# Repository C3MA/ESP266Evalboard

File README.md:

# ESP8266Evalboard

The purpose of this project is to provide open source based home automation inspiration. It consists of one or more ESP8266 evaluation boards with sensors and actors which connect to a raspberry pi with openhab.

For further documentation, look up the Docu folder in this repository.

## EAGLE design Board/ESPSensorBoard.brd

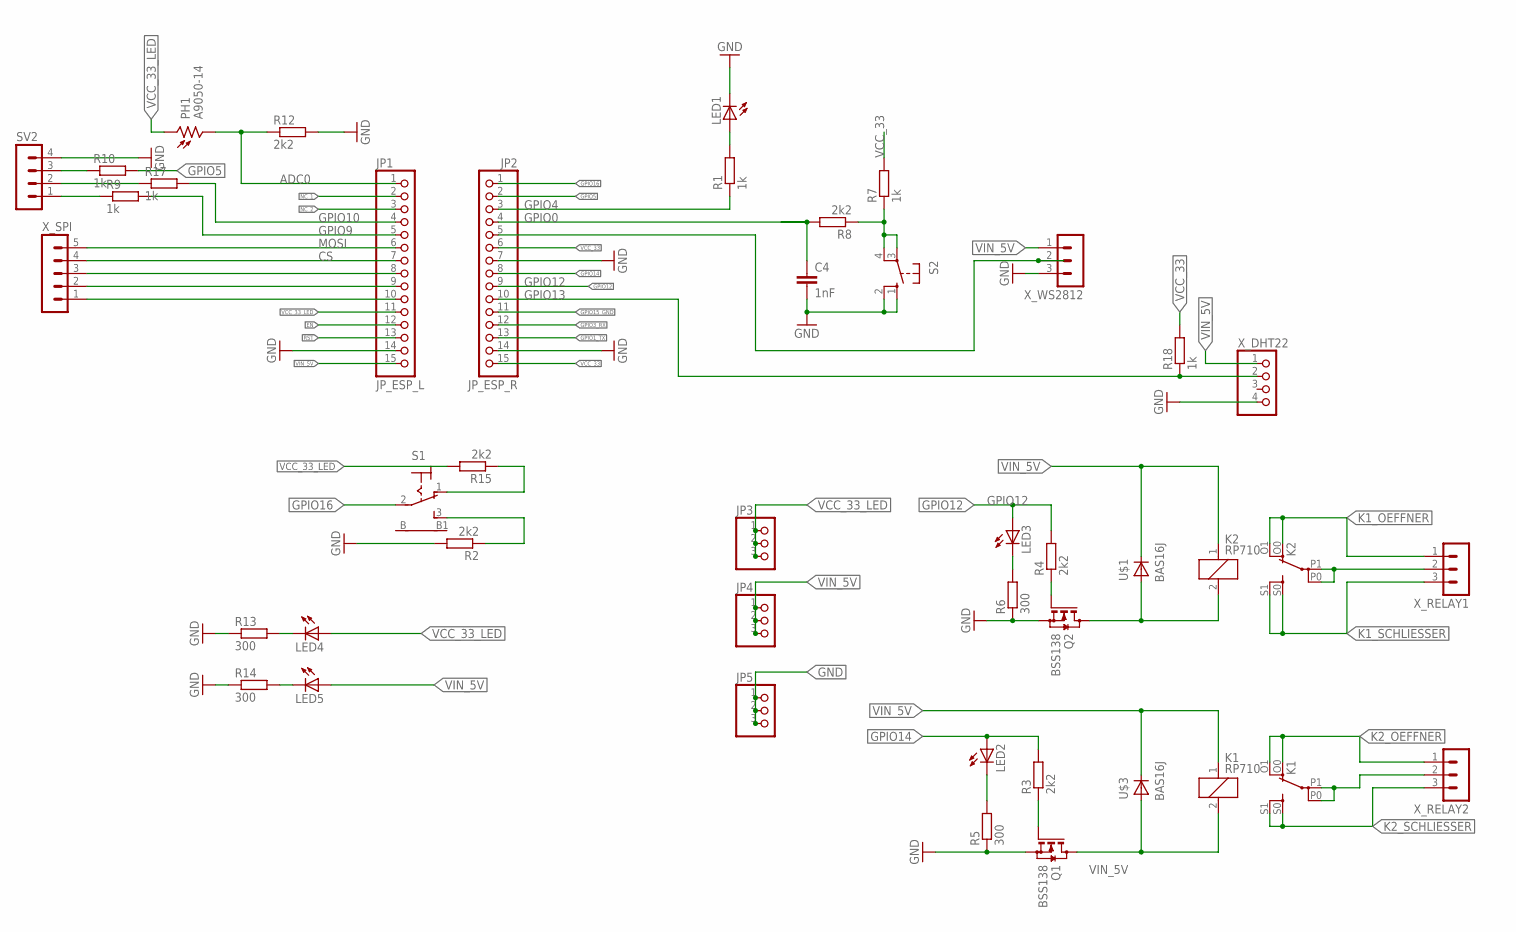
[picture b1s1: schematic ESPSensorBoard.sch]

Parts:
C4: 1nF; C0805K
JP1: JP_ESP_L; 1X15
JP2: JP_ESP_R; 1X15
JP3, JP4, JP5: PINHD-1X3; 1X03
K1, K2: RP710
LED1: LED5MM
LED2, LED3, LED4, LED5: LED3MM
PH1: A9050-14; M9960
Q1, Q2: BSS138; SOT23
R1, R7, R9, R10, R17, R18: 1k; R0805
R2, R3, R4, R8, R12, R15: 2k2; R0805
R5, R6, R13, R14: 300; R0805
S1: LPV-1
S2: 10-XX; B3F-10XX
SV2: MA04-1
U$1, U$3: BAS16J; 0805-POL
X_DHT22: PINHD-1X4; 1X04
X_RELAY1, X_RELAY2: MA03-1
X_SPI: MA05-1
X_WS2812: MA03-1

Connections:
ADC0: JP1.1, PH1.2, R12.1
CS: JP1.7, X_SPI.4
EN: JP1.12
GND: C4.2, JP1.14, JP2.7, JP2.14, JP5.1, JP5.2, JP5.3, LED1.K (C), Q1.2 (S), Q2.2 (S), R2.2, R5.1, R6.1, R12.2, R13.1, R14.1, S2.1 (S), S2.2 (S1), SV2.4, X_DHT22.4, X_WS2812.3
GPIO0: C4.1, JP2.4, R8.2
GPIO1_TX: JP2.13
GPIO2: JP2.5, X_WS2812.2
GPIO3_RX: JP2.12
GPIO4: JP2.3, R1.1
GPIO5: JP2.2, R10.2
GPIO9: JP1.5, R9.2
GPIO10: JP1.4, R17.2
GPIO12: JP2.9, LED3.A, R4.2
GPIO13: JP2.10, R18.1, X_DHT22.2
GPIO14: JP2.8, LED2.A, R3.2
GPIO15_GND: JP2.11
GPIO16: JP2.1, S1.2
K1_OEFFNER: K2.O0 (O), K2.O1 (O), X_RELAY1.1
K1_SCHLIESSER: K2.S0 (S), K2.S1 (S), X_RELAY1.3
K2_OEFFNER: K1.O0 (O), K1.O1 (O), X_RELAY2.1
K2_SCHLIESSER: K1.S0 (S), K1.S1 (S), X_RELAY2.3
MOSI: JP1.6, X_SPI.5
unnamed: R2.1, S1.3 (S)
unnamed: Q2.1 (G), R4.1
unnamed: LED1.A, R1.2
unnamed: Q1.1 (G), R3.1
unnamed: R9.1, SV2.1
unnamed: R10.1, SV2.3
unnamed: K1.P0, K1.P1, X_RELAY2.2
unnamed: K1.2, Q1.3 (D), U$3.A
unnamed: LED4.K (C), R13.2
unnamed: JP1.8, X_SPI.3
unnamed: K2.P0, K2.P1, X_RELAY1.2
unnamed: K2.2, Q2.3 (D), U$1.A
unnamed: LED2.K (C), R5.2
unnamed: LED3.K (C), R6.2
unnamed: R7.1, R8.1, S2.3, S2.4 (P1)
unnamed: LED5.K (C), R14.2
unnamed: JP1.9, X_SPI.2
unnamed: JP1.10, X_SPI.1
unnamed: R17.1, SV2.2
unnamed: R15.1, S1.1 (O)
NC_1: JP1.2
NC_2: JP1.3
RST: JP1.13
VCC_33: JP2.6, JP2.15, R7.2, R18.2
VCC_33_LED: JP1.11, JP3.1, JP3.2, JP3.3, LED4.A, PH1.1, R15.2
VIN_5V: JP1.15, JP4.1, JP4.2, JP4.3, K1.1, K2.1, LED5.A, U$1.K (C), U$3.K (C), X_DHT22.1, X_WS2812.1

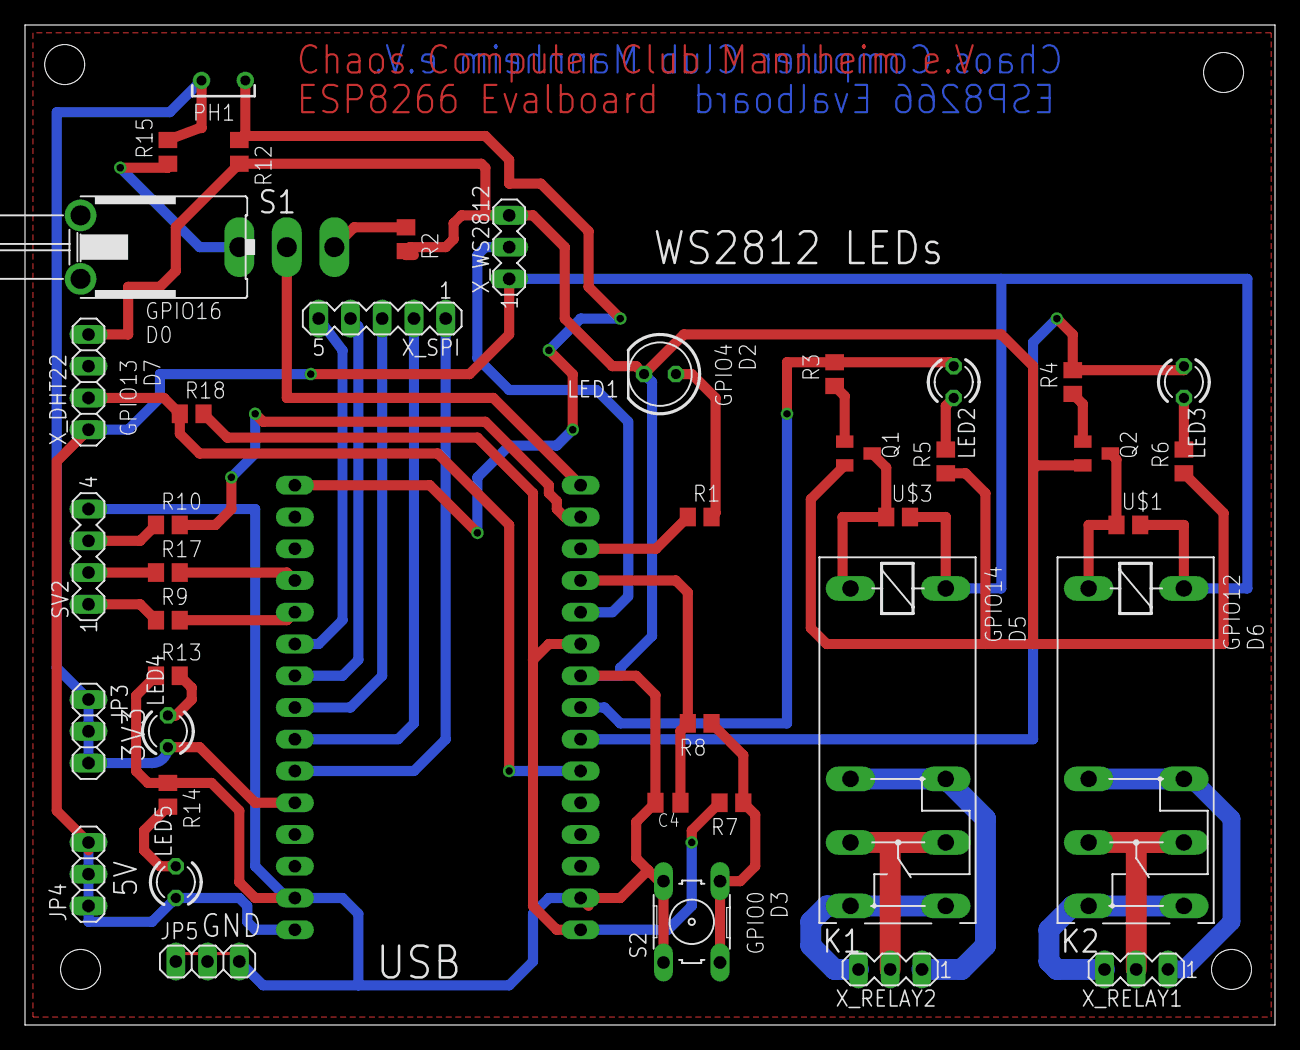
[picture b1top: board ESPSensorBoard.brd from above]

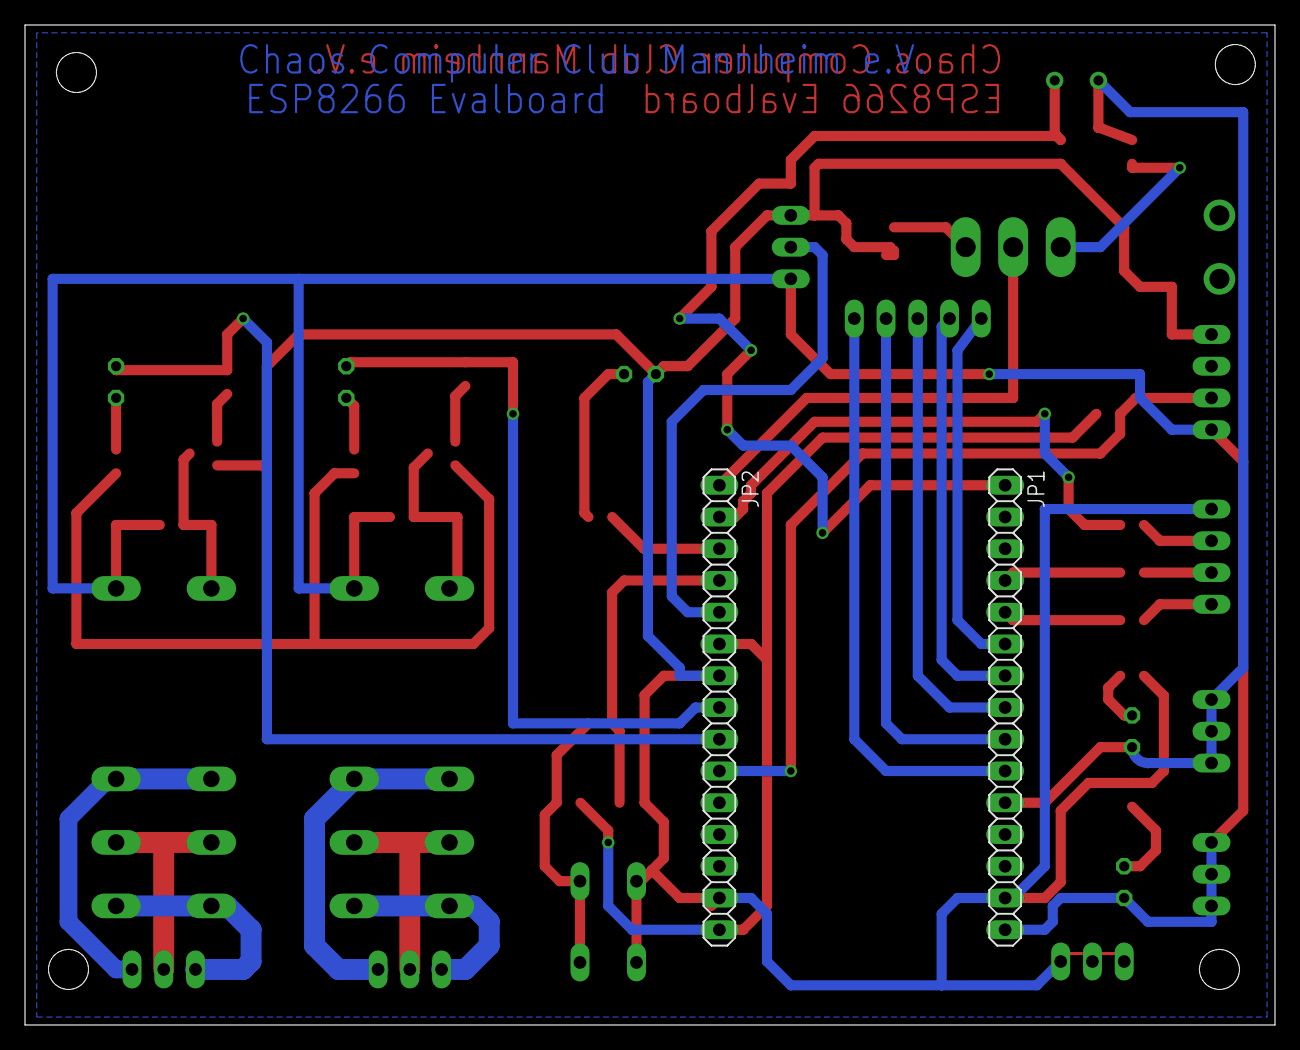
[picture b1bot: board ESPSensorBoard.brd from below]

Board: 2 copper layers, 100.0 x 80.0 mm, 42 parts (2 on the bottom side), 41 nets.

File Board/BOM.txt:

Partlist

Exported from ESPSensorBoard.sch at 12.07.17 18:20

EAGLE Version 6.6.0 Copyright (c) 1988-2014 CadSoft

Assembly variant: 

Part     Value          Device     Package  Library                 Sheet

C4       1nF            C-EUC0805K C0805K   rcl                     1
JP1      JP_ESP_L       PINHD-1X15 1X15     pinhead                 1
JP2      JP_ESP_R       PINHD-1X15 1X15     pinhead                 1
JP3                     PINHD-1X3  1X03     pinhead                 1
JP4                     PINHD-1X3  1X03     pinhead                 1
JP5                     PINHD-1X3  1X03     pinhead                 1
K1       RP710          RP710      RP710    relay                   1
K2       RP710          RP710      RP710    relay                   1
LED1                    LED5MM     LED5MM   led                     1
LED2                    LED3MM     LED3MM   led                     1
LED3                    LED3MM     LED3MM   led                     1
LED4                    LED3MM     LED3MM   led                     1
LED5                    LED3MM     LED3MM   led                     1
PH1      A9050-14       M9960_11A  M9960    photo-elements          1
Q1       BSS138         BSS123     SOT23    transistor-small-signal 1
Q2       BSS138         BSS123     SOT23    transistor-small-signal 1
R1       1k             R          R0805    eagle-ltspice           1
R2       2k2            R          R0805    eagle-ltspice           1
R3       2k2            R-EU_R0805 R0805    rcl                     1
R4       2k2            R-EU_R0805 R0805    rcl                     1
R5       300            R-EU_R0805 R0805    rcl                     1
R6       300            R-EU_R0805 R0805    rcl                     1
R7       1k             R-EU_R0805 R0805    rcl                     1
R8       2k2            R-EU_R0805 R0805    rcl                     1
R9       1k             R          R0805    eagle-ltspice           1
R10      1k             R          R0805    eagle-ltspice           1
R12      2k2            R          R0805    eagle-ltspice           1
R13      300            R-EU_R0805 R0805    rcl                     1
R14      300            R-EU_R0805 R0805    rcl                     1
R15      2k2            R          R0805    eagle-ltspice           1
R17      1k             R          R0805    eagle-ltspice           1
R18      1k             R          R0805    eagle-ltspice           1
S1                      LPV-1      LPV-1    switchmodified          1
S2                      10-XX      B3F-10XX switch-omron            1
SV2                     MA04-1     MA04-1   con-lstb                1
U$1      BAS16J         BAS16J     0805-POL thomas2012              1
U$3      BAS16J         BAS16J     0805-POL thomas2012              1
X_DHT22                 PINHD-1X4  1X04     pinhead                 1
X_RELAY1                MA03-1     MA03-1   con-lstb                1
X_RELAY2                MA03-1     MA03-1   con-lstb                1
X_SPI                   MA05-1     MA05-1   con-lstb                1
X_WS2812                MA03-1     MA03-1   con-lstb                1

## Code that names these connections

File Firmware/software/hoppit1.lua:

-- HoppIT Test
gpio.mode(2, gpio.OUTPUT,gpio.PULLUP) -- GPIO4
gpio.mode(6, gpio.OUTPUT, gpio.PULLUP) -- GPIO12
gpio.mode(5, gpio.OUTPUT, gpio.PULLUP) -- GPIO14
gpio.write(2, gpio.LOW)
gpio.write(6, gpio.LOW)
gpio.write(5, gpio.LOW)

gpio.write(2, gpio.HIGH)
gpio.write(6, gpio.HIGH)
gpio.write(5, gpio.HIGH)
print("LED test done")
gpio.write(5, gpio.LOW)

gpio.mode(0, gpio.INPUT)
gpio.mode(3, gpio.INPUT)
tmr.alarm(0, 500, tmr.ALARM_AUTO, function()
    print("Button: at GPIO0  " .. gpio.read(3))
    print("Switch: at GPIO16 " .. gpio.read(0))
    print("Analog: at ADC    " .. adc.read(0) )
    -- Button to LED
    gpio.write(2, gpio.read(3))
    -- Switch to relais
    gpio.write(6, gpio.read(0))
    gpio.write(5, gpio.read(0))

    rgbTemp=0
    rgbHumi=0
    -- Read Temperature and Humidity
    status, temp, humi, temp_dec, humi_dec = dht.read(7) -- GPIO13
    if status == dht.OK then
        -- Integer firmware using this example
        print(string.format("DHT Temperature:%d.%03d;Humidity:%d.%03d\r\n",
              math.floor(temp),
              temp_dec,
              math.floor(humi),
              humi_dec
        ))
    
        -- Float firmware using this example
        rgbTemp=math.floor((temp-25)*15) -- Start with 20 degree
        rgbTemp=math.min(255, math.max(rgbTemp, 0))
        rgbHumi=math.min(255, math.max(math.floor((humi)/5), 0))

        
        print("DHT Temperature:"..temp..";".."Humidity:"..humi .." RGB Temp value: " .. rgbTemp .. " RGB Hmidity: " .. rgbHumi)
        
    elseif status == dht.ERROR_CHECKSUM then
        print( "DHT Checksum error." )
    elseif status == dht.ERROR_TIMEOUT then
        print( "DHT timed out." )
    end
    -- Set the color LEDs
    
    ws2812.write(string.char(adc.read(0)/10, 0, 0) .. string.char(0, rgbTemp, 0) .. string.char(0, 0, rgbHumi))
end)
ws2812.init()
ws2812.write(string.char(32, 0, 0) .. string.char(0, 32, 0) .. string.char(0, 0, 32))

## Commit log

2017-12-15 Board layout added
2017-12-15 Firmware and Software added
2017-12-26 First version of the documation
2017-12-26 Minor Text fixes
2017-12-26 Some readme
2018-01-12 fixed typo
